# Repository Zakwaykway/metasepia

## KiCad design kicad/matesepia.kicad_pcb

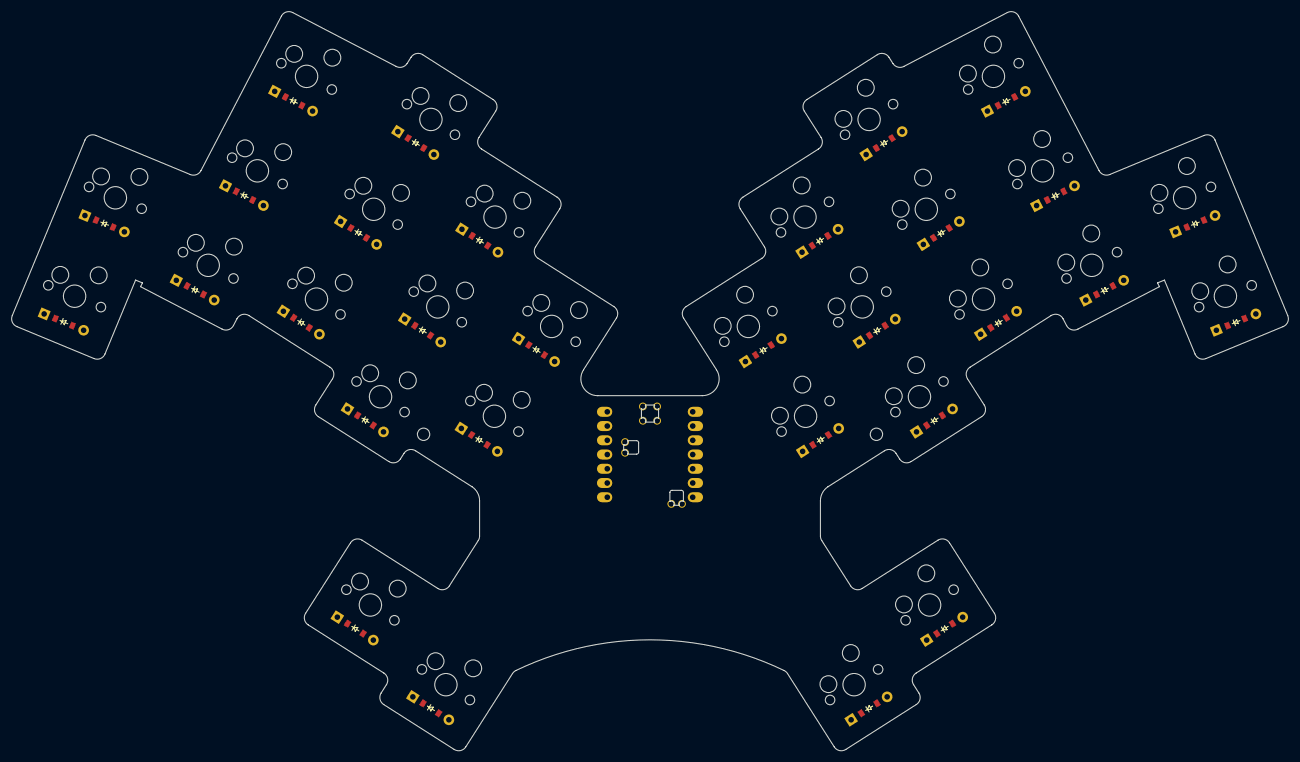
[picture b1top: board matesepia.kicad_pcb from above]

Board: 2 copper layers, 227.7 x 131.8 mm, 63 parts (0 on the bottom side), 42 nets, no tracks yet.

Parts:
D1, D2, D3, D4, D5, D6, D7, D8, D9, D10, D11, D12, D13, D14, D15, D16, D17, D18, D19, D20, D21, D22, D23, D24, D25, D26, D27, D28, D29, D30: ComboDiode
MCU1: xiao-ble; XIAO-BLE
MH1, MH2: mounting_hole_npth
S1, S2, S3, S4, S5, S6, S7, S8, S9, S10, S11, S12, S13, S14, S15, S16, S17, S18, S19, S20, S21, S22, S23, S24, S25, S26, S27, S28, S29, S30: MX

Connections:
GND: MCU1.13, MCU1.17
P0: MCU1.1, S2.1, S8.1, S13.1, S18.1, S24.1
P1: MCU1.2, S5.1, S11.1, S15.1, S21.1, S26.1
P2: MCU1.3, S1.1, S7.1, S12.1, S17.1, S23.1
P3: MCU1.4, S4.1, S10.1, S14.1, S20.1, S25.1
P4: MCU1.5, S3.1, S9.1, S19.1, S28.1, S29.1
P5: MCU1.6, S6.1, S16.1, S22.1, S27.1, S30.1
P6: D1.1, D2.1, D3.1, D4.1, D5.1, D6.1, MCU1.7
P7: D7.1, D8.1, D9.1, D10.1, D11.1, D27.1, MCU1.8
P8: D12.1, D13.1, D22.1, D25.1, D26.1, D28.1, MCU1.9
P9: D16.1, D19.1, D20.1, D21.1, D23.1, D24.1, MCU1.10
P10: D14.1, D15.1, D17.1, D18.1, D29.1, D30.1, MCU1.11
index_bottom: D9.2, S9.2
index_home: D10.2, S10.2
index_top: D11.2, S11.2
inner_home: D12.2, S12.2
inner_top: D13.2, S13.2
middle_bottom: D6.2, S6.2
middle_home: D7.2, S7.2
middle_top: D8.2, S8.2
mirror_index_bottom: D22.2, S22.2
mirror_index_home: D23.2, S23.2
mirror_index_top: D24.2, S24.2
mirror_inner_home: D25.2, S25.2
mirror_inner_top: D26.2, S26.2
mirror_middle_bottom: D19.2, S19.2
mirror_middle_home: D20.2, S20.2
mirror_middle_top: D21.2, S21.2
mirror_pinky_bottom: D14.2, S14.2
mirror_pinky_home: D15.2, S15.2
mirror_reachy_default: D30.2, S30.2
mirror_ring_bottom: D16.2, S16.2
mirror_ring_home: D17.2, S17.2
mirror_ring_top: D18.2, S18.2
mirror_tucky_default: D29.2, S29.2
pinky_bottom: D1.2, S1.2
pinky_home: D2.2, S2.2
reachy_default: D28.2, S28.2
ring_bottom: D3.2, S3.2
ring_home: D4.2, S4.2
ring_top: D5.2, S5.2
tucky_default: D27.2, S27.2

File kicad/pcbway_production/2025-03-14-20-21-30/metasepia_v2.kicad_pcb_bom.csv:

Designator,Quantity,Value,Footprint,Package,MPN,DNP,Mount_Type
"D1, D10, D11, D12, D13, D14, D15, D16, D17, D18, D19, D2, D20, D21, D22, D23, D24, D25, D26, D27, D28, D29, D3, D30, D4, D5, D6, D7, D8, D9",30,,diode,,,,tht
MCU1,1,xiao-ble,xiao-smd,,,,smt
"S1, S10, S11, S12, S13, S14, S15, S16, S17, S18, S19, S2, S20, S21, S22, S23, S24, S25, S26, S27, S28, S29, S3, S30, S4, S5, S6, S7, S8, S9",30,,hsmx,,,,smt
"_1, _2, _3, _4",4,,m2hole,,,,tht
